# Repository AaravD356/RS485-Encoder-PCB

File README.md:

# Arm-Encoder-PCB

RS485 encoder interface board for accurate joint position feedback on the **UMD Mars Rover Team's** autonomous arm. The board polls a multi-drop bus of RS485 absolute encoders and relays live position and velocity data over CAN to the rest of the rover's control system, with an STM32 handling the protocol translation.

## Overview

Each joint on the autonomous arm is fitted with an RS485 absolute encoder (AMT21x / AMT212 series). This board's STM32 firmware manages a bus of these encoders, round-robin polling each one, validating the returned data, and tracking position/velocity per node. That data is exposed over CAN so the arm's main controller can request live feedback for any specific joint on demand.

## Node Addressing

Each encoder on the bus is assigned a unique node ID, sent directly as the command byte for a standard position read:

Up to a configurable max number of encoders can be registered at once, each tracked independently with its own node ID, resolution, poll period, last-known position, and online/offline status. Four encoders are loaded by default at startup, but encoders can be added or cleared at runtime, with duplicate node IDs rejected.

## Bus Polling

The system round-robins through registered encoders rather than polling all of them every cycle, respecting each encoder's individual poll period. Each controller cycle:
1. Checks whether the current encoder's poll interval has elapsed.
2. If due, sends that encoder's node-addressed command and reads back the 2-byte response.
3. Validates the response using the AMT21 parity check (two check bits derived from the data payload).
4. Decodes the position from the response, scaled to the encoder's configured resolution (up to 14-bit).
5. Computes velocity from the position delta between reads, unwrapping across the resolution's modulo range to handle wraparound at the 0/max boundary.
6. Advances to the next encoder for the following cycle.

Encoders that fail to respond or fail checksum validation are marked offline, with failed/successful read counters tracked per node — this lets the system distinguish a genuinely disconnected encoder from an occasional dropped packet.

## RS485 Transport

Direction control (TX/RX switching) is handled either automatically by the UART hardware or manually via a GPIO-driven DE pin, depending on configuration. Before every transmission, the receive buffer is flushed to avoid stale data corrupting the next read. Transmit completion is polled with a timeout rather than assumed, so a bus fault or non-responding node can't hang the polling loop indefinitely.

## CAN Integration

The board exposes encoder data over CAN request/response:

- **Request** — the controller specifies a target encoder's node ID.
- **Response** — the board replies with that node's ID, position (in 0.1° units), and velocity (in 0.01°/s units), scaled from raw encoder counts based on the encoder's resolution.

Requests are matched to a registered encoder by node ID; if the encoder isn't found or isn't currently online, no meaningful data is returned. This request/response model means the main controller can poll specific joints on demand rather than needing to parse a continuous broadcast stream.

## Reliability Notes

- Per-node online/offline tracking rather than a single global "encoder ok" flag
- Failed reads don't stall the polling loop — the round-robin simply moves to the next node
- Position wraparound is explicitly handled in velocity calculation, avoiding large erroneous velocity spikes when an encoder crosses its zero point
- Duplicate node IDs are rejected at registration, preventing bus address collisions from being configured accidentally

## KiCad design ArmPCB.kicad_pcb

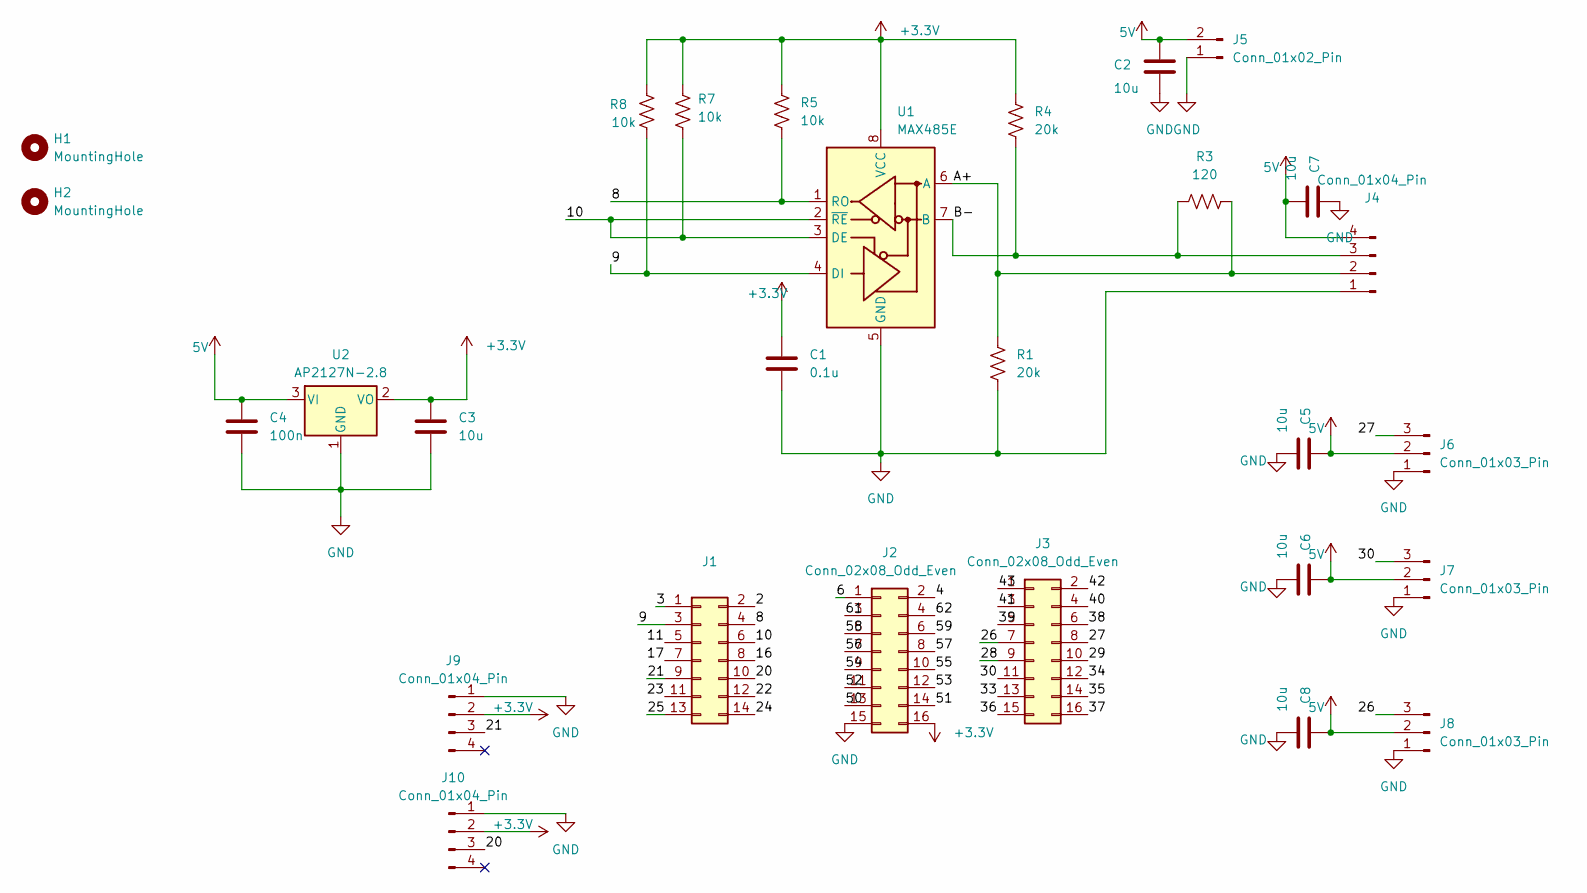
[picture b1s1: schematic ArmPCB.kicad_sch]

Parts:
C1: 0.1u; C_0402_1005Metric_Pad0.74x0.62mm_HandSolder
C2, C3, C5, C6, C7, C8: 10u; C_0402_1005Metric_Pad0.74x0.62mm_HandSolder
C4: 100n; C_0402_1005Metric_Pad0.74x0.62mm_HandSolder
H1, H2: MountingHole; MountingHole_3.2mm_M3_DIN965
J1: Conn_02x07_Odd_Even; PinHeader_2x07_P2.54mm_Vertical
J2, J3: Conn_02x08_Odd_Even; PinHeader_2x08_P2.54mm_Vertical
J4: Conn_01x04_Pin; JST_XH_S4B-XH-A_1x04_P2.50mm_Horizontal
J5: Conn_01x02_Pin; JST_XH_S2B-XH-A_1x02_P2.50mm_Horizontal
J6, J7, J8: Conn_01x03_Pin; JST_XH_S3B-XH-A_1x03_P2.50mm_Horizontal
J9, J10: Conn_01x04_Pin; JST_PH_S4B-PH-K_1x04_P2.00mm_Horizontal
R1, R4: 20k; R_0402_1005Metric_Pad0.72x0.64mm_HandSolder
R3: 120; R_0402_1005Metric_Pad0.72x0.64mm_HandSolder
R5, R7, R8: 10k; R_0402_1005Metric_Pad0.72x0.64mm_HandSolder
U1: MAX485E; SOIC-8_3.9x4.9mm_P1.27mm
U2: AP2127N-2.8; SOT-223-3_TabPin2

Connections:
5V: C2.1, C4.1, C5.1, C6.1, C7.2, C8.1, J4.4, J5.2, J6.2, J7.2, J8.2, U2.3 (VI)
+3.3V: C1.1, C3.1, J2.16, J9.2, J10.2, R4.2, R5.1, R7.1, R8.1, U1.8 (VCC), U2.2 (VO)
/2: J1.2
/3: J1.1
/4: J2.2
/6: J2.1
/8: J1.4, R5.2, U1.1 (RO)
/9: J1.3, R8.2, U1.4 (DI)
/10: J1.6, R7.2, U1.2 (~RE), U1.3 (DE)
/11: J1.5
/16: J1.8
/17: J1.7
/20: J1.10, J10.3
/21: J1.9, J9.3
/22: J1.12
/23: J1.11
/24: J1.14
/25: J1.13
/26: J3.7, J8.3
/27: J3.8, J6.3
/28: J3.9
/29: J3.10
/30: J3.11, J7.3
/33: J3.13
/34: J3.12
/35: J3.14
/36: J3.15
/37: J3.16
/38: J3.6
/39: J3.5
/40: J3.4
/41: J3.3
/42: J3.2
/43: J3.1
/50: J2.13
/51: J2.14
/52: J2.11
/53: J2.12
/54: J2.9
/55: J2.10
/56: J2.7
/57: J2.8
/58: J2.5
/59: J2.6
/61: J2.3
/62: J2.4
/A+: J4.2, R1.1, R3.2, U1.6 (A)
/B-: J4.3, R3.1, R4.1, U1.7 (B)
GND: C1.2, C2.2, C3.2, C4.2, C5.2, C6.2, C7.1, C8.2, J2.15, J4.1, J5.1, J6.1, J7.1, J8.1, J9.1, J10.1, R1.2, U1.5 (GND), U2.1 (GND)

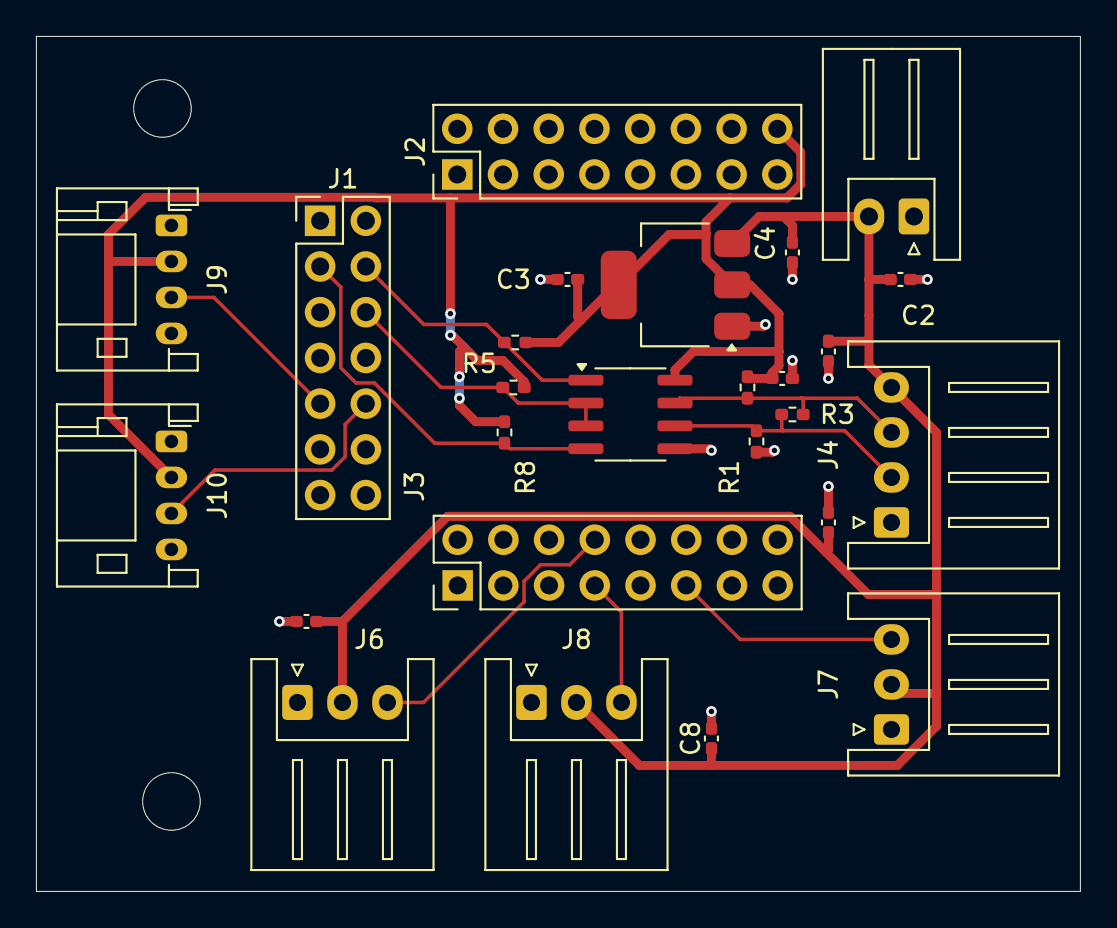
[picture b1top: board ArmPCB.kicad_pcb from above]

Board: 2 copper layers, 58.0 x 47.5 mm, 28 parts (0 on the bottom side), 13 nets.
